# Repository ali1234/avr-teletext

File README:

avr-teletext
------------

This is a teletext inserter for AVR microcontroller. It adds teletext to an
existing composite signal. It is controlled on I2C and features two modes.
In passthrough mode whole teletext packets are received on I2C and inserted
into the video signal, allowing the broadcast of an interleaved magazine with
multiple pages. In console mode the I2C port receives individual characters
and emulates a framebuffer by generating a single page repeatedly. The console
supports accelerated scrolling.

A video of the device operating is here:
https://plus.google.com/117474986382867317779/posts/eKBn5ePYWbc

Hardware
--------

The hardware schematic is in schematic.png. General parts list:

 * AVR microcontroller. I used Atmega 168. Using a part with more RAM would
   allow for multiple consoles are other fancy stuff.

 * LM1881 sync splitter. For generating horizontal and vertical sync pulses.
   Hard to find in through hole package. I got it at http://www.rapidonline.com

 * 13.875 MHz crystal. For AVR clock. This is double teletext frequency.
   Extremely hard to find. I got it from http://quarndon.co.uk/

 * A diode to hook up the teletext to the video signal.

 * Various resistors and capacitors. Especially you need some filter caps 
   between ground and vcc or the output signal will be too dirty to work.

I2C addresses
-------------

The AVR implements two I2C addresses: data and control.

0x00 - Data address

Bits    Function
0-6     7 bit characters written here will be placed into the output buffer.
7       Unused.

0x01 - Control address

Bits
0       Set mode. 0 = console, 1 = passthrough.
1-7     Unused.

Console mode
------------

In this mode each character received will be written into a character
framebuffer, staring in the top left corner and moving to the right with each 
character. When the end of the line is reached the cursor position moves to the
beginning of the next line. When the bottom of the display is reached the row
pointers into the buffer are shifted by 1 line, and the line at the top of the 
display becomes the line at the bottom. This line is cleared and new characters
go here. Essentially it is a scrolling text console. Newlines are supported.
Setting the cursor position is not supported. The whole buffer is output on a 
loop regardless of whether new data is available.

Passthrough mode
----------------

In this mode each received character is written into the output buffer and then
outputted only once. The buffer is used with a head and tail pointer here. When
a row fills up the head pointer is incremented and when the row is output the 
tail pointer is incremented. If there are no lines to output a filler line is
output instead. This mode is intended to be used to broadcast normal teletext
magazines with multiple interleaved pages.

The Diode
---------
 
The AVR uses SPI to output the teletext signal. The ISR enables TX in the
horizontal interrupt before pushing out the bits at the right moment and 
disables TX afterwards. This is neccessary, because TX would be high when
idle. The original code dealed with it by producing an inverted signal, 
which would later be inverted/coupled with an 74LS244N.

When the teletext generator is idle or goes low, then the circuit should
be disconnected from video, so that the low state does not drain current
from the video signal. This is achieved using a diode. In fact a LED could 
be used which, together with the right resistor value, would produce the 
right voltage level and even indicate data transmission with a flickering 
light. 

During blanking, video has negative levels agains low, but most diodes have
a much larger forwad bias than that difference.

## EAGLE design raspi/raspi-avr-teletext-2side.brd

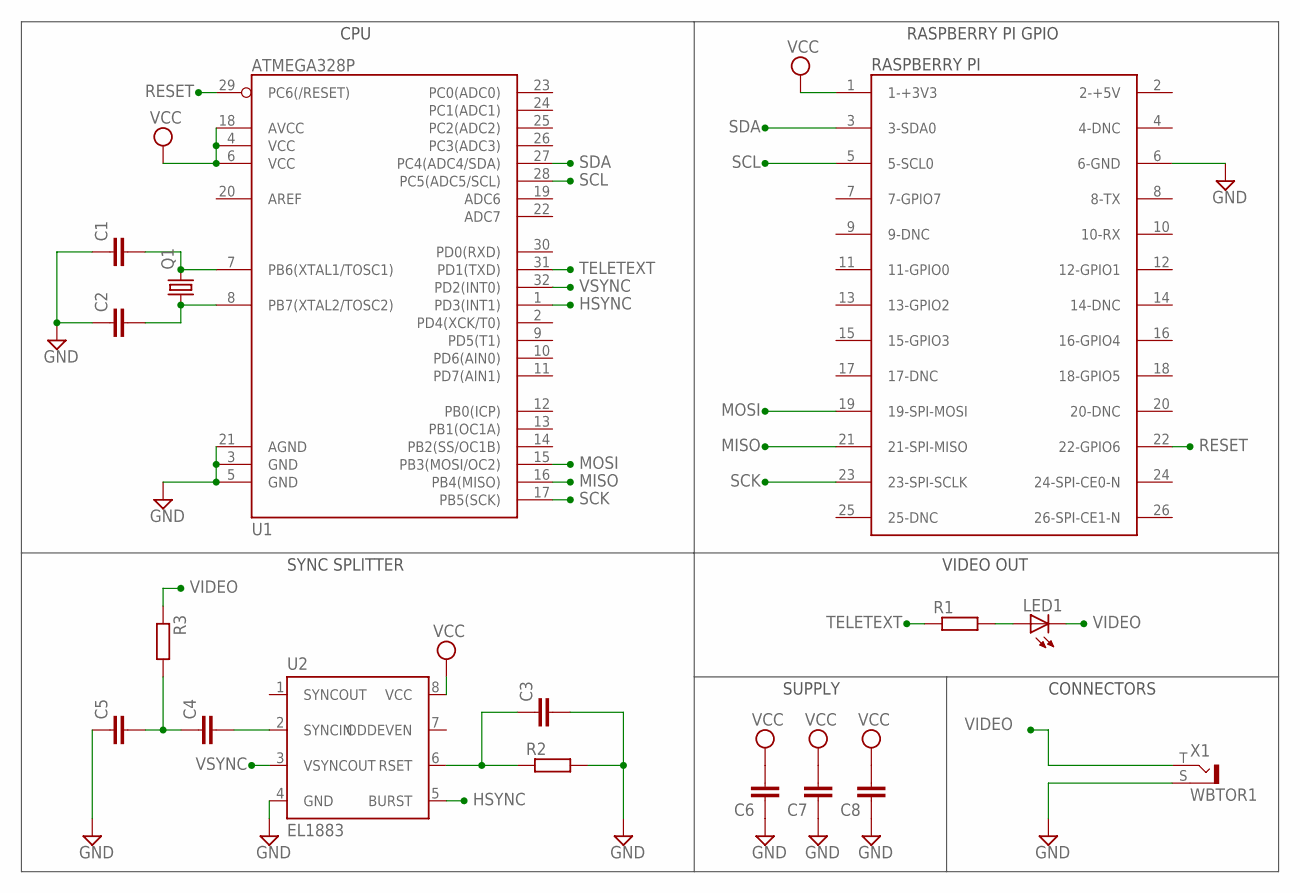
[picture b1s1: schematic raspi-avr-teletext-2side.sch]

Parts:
C1, C2, C3, C4, C5, C6, C7, C8: C-EUC0603; C0603
D1: RASPBERRY-PI
LED1: LEDCHIP-LED0603; CHIP-LED0603
Q1: CRYSTALHC49U-V; HC49U-V
R1, R2, R3: R-EU_R0603; R0603
U1: ATMEGA328P; TQFP32-08
U2: EL1883; SOIC8
X1: WBTOR1

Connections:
GND: C1.1, C2.1, C3.2, C5.1, C6.1, C7.1, C8.1, D1.6 (6-GND), R2.2, U1.3 (GND), U1.5 (GND), U1.21 (AGND), U2.4 (GND), X1.S
HSYNC: U1.1 (PD3(INT1)), U2.5 (BURST)
MISO: D1.21 (21-SPI-MISO), U1.16 (PB4(MISO))
MOSI: D1.19 (19-SPI-MOSI), U1.15 (PB3(MOSI/OC2))
unnamed: C1.2, Q1.2, U1.7 (PB6(XTAL1/TOSC1))
unnamed: C2.2, Q1.1, U1.8 (PB7(XTAL2/TOSC2))
unnamed: C3.1, R2.1, U2.6 (RSET)
unnamed: LED1.A, R1.2
unnamed: C4.2, U2.2 (SYNCIN)
unnamed: C4.1, C5.2, R3.2
RESET: D1.22 (22-GPIO6), U1.29 (PC6(/RESET))
SCK: D1.23 (23-SPI-SCLK), U1.17 (PB5(SCK))
SCL: D1.5 (5-SCL0), U1.28 (PC5(ADC5/SCL))
SDA: D1.3 (3-SDA0), U1.27 (PC4(ADC4/SDA))
TELETEXT: R1.1, U1.31 (PD1(TXD))
VCC: C6.2, C7.2, C8.2, D1.1 (1-+3V3), U1.4 (VCC), U1.6 (VCC), U1.18 (AVCC), U2.8 (VCC)
VIDEO: LED1.C, R3.1, X1.T
VSYNC: U1.32 (PD2(INT0)), U2.3 (VSYNCOUT)

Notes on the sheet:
RASPBERRY PI
SYNC SPLITTER
CPU
RASPBERRY PI GPIO
VIDEO OUT
SUPPLY
CONNECTORS

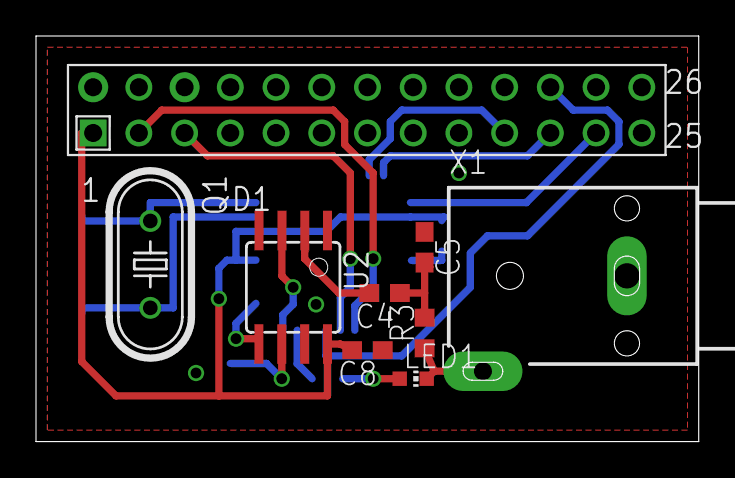
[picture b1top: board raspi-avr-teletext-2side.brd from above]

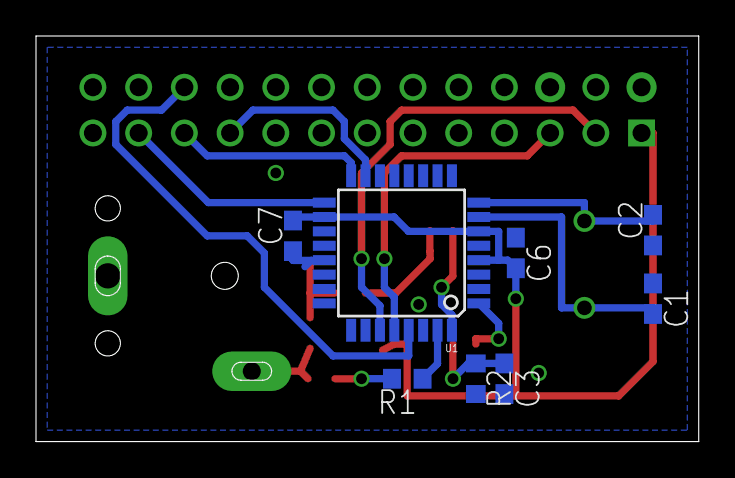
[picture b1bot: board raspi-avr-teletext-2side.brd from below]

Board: 2 copper layers, 36.8 x 22.5 mm, 17 parts (8 on the bottom side), 18 nets.

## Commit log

2012-02-01 Initial commit.
2012-02-05 Use proper register names. Move around some things to make sure uart doesn't underflow.
2012-11-06 Fixup some i2c stuff.
2012-11-06 Add license.
2012-11-06 Add schematic.
2012-11-06 Add README
2012-11-06 Update docs
2012-11-06 Add video link to docs.
2012-11-06 Fix the year on copyright message.
2013-10-05 Use a nicer delay macro.
2013-10-05 Replace buffer/inverter with a diode.
    Turn off the Tx hardware so it doesn't pull the line high
    when there is no data. Don't invert the data before writing
    it out.
2013-10-05 Allow device selection in Makefile
    Conflicts:
    Makefile
2013-10-05 Don't clobber registers in ISR.
2013-10-05 Use CLR instead of LDI to zero registers.
2013-10-05 ISR has to restore r1 to whatever it's previous value was, not 0.
    r1 equals 0 by convention, but interrupt may happen in the middle
    of a function before the value is restored.
2013-10-05 Schematics for Raspberry Pi extension board.
2013-10-06 Fix MOSI/MISO
    I can never remember whether you are supposed to flip these or not.

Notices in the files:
parts and their libraries:
SparkFun-DigitalIC: Licensing: CC v3.0 Share-Alike You are welcome to use this library for commercial purposes.
